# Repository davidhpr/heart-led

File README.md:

# Heart LED PCB
This is a simple PCB, designed to be in the shape of heart. There is a SPST switch for turning on/off the power. It is powered by a battery of 9V. Resistor values are adapted for red LEDs. Color changing requires resistor dimensioning.

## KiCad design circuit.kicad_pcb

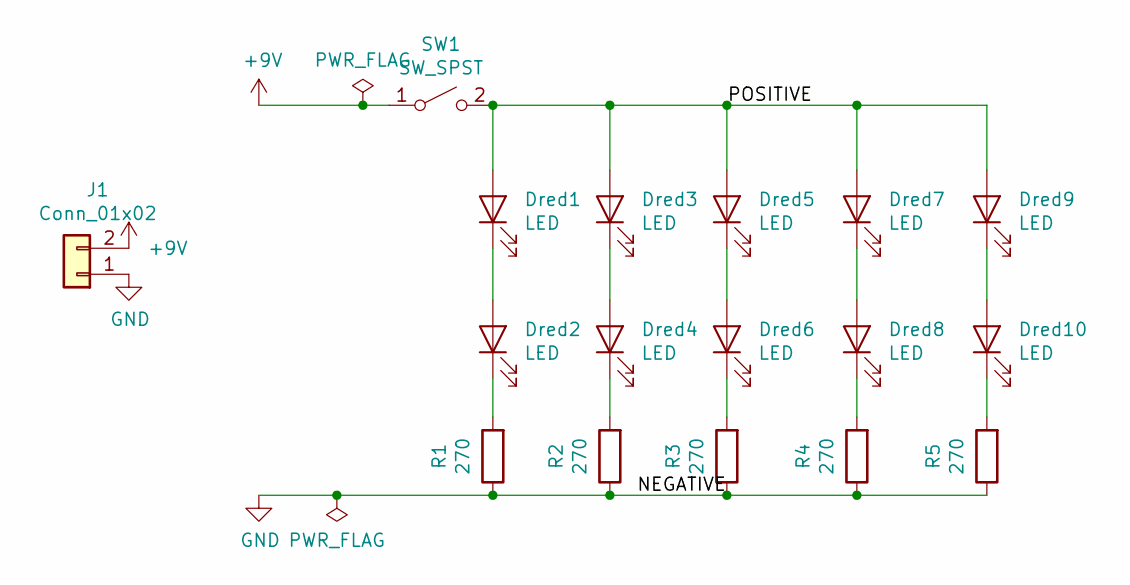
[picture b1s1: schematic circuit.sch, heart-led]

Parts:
Dred1, Dred2, Dred3, Dred4, Dred5, Dred6, Dred7, Dred8, Dred9, Dred10: LED; LED_D3.0mm
J1: Conn_01x02; PinHeader_1x02_P1.00mm_Horizontal
R1, R2, R3, R4, R5: 270; R_Axial_DIN0207_L6.3mm_D2.5mm_P2.54mm_Vertical
SW1: SW_SPST; SW_DIP_SPSTx01_Slide_6.7x4.1mm_W7.62mm_P2.54mm_LowProfile

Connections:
+9V: J1.2, SW1.1 (A)
/POSITIVE: Dred1.2 (A), Dred3.2 (A), Dred5.2 (A), Dred7.2 (A), Dred9.2 (A), SW1.2 (B)
GND: J1.1, R1.1, R2.1, R3.1, R4.1, R5.1
unnamed: Dred1.1 (K), Dred2.2 (A)
unnamed: Dred2.1 (K), R1.2
unnamed: Dred3.1 (K), Dred4.2 (A)
unnamed: Dred4.1 (K), R2.2
unnamed: Dred5.1 (K), Dred6.2 (A)
unnamed: Dred6.1 (K), R3.2
unnamed: Dred7.1 (K), Dred8.2 (A)
unnamed: Dred8.1 (K), R4.2
unnamed: Dred10.1 (K), R5.2
unnamed: Dred9.1 (K), Dred10.2 (A)

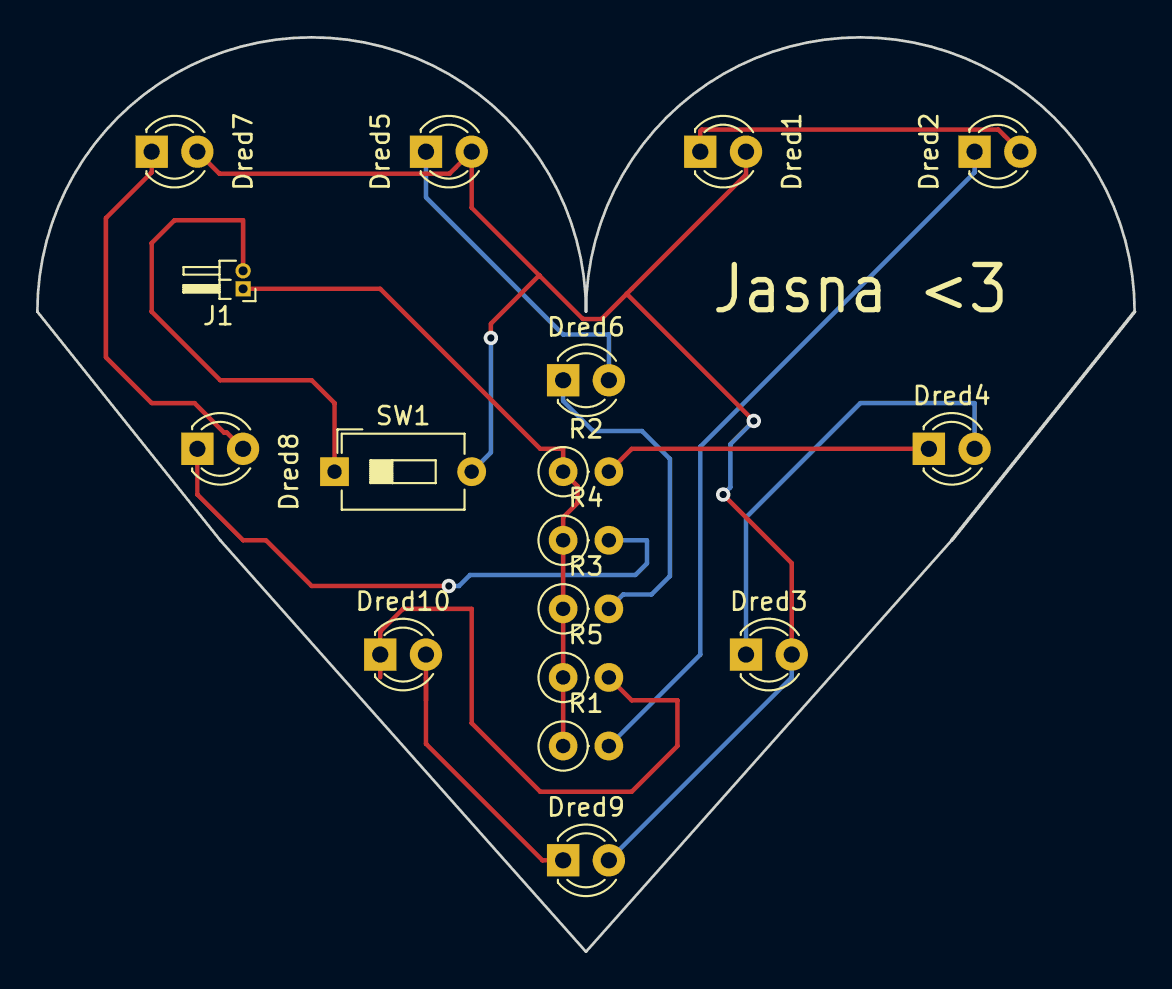
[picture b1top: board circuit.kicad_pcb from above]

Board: 2 copper layers, 60.9 x 50.8 mm, 17 parts (0 on the bottom side), 13 nets.
